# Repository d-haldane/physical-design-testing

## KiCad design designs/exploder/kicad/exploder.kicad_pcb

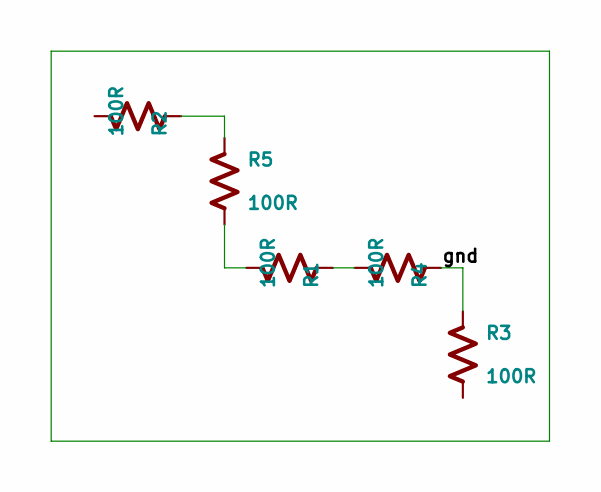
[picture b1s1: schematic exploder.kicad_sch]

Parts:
R1, R2, R3, R4, R5: 100R; Pkg0402; MPN RQ73C1E100RBTD

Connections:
gnd: R3.2, R4.1
r0_p1: R2.1, R5.2
r1_p1: R1.2, R5.1
r2_p1: R1.1, R4.2

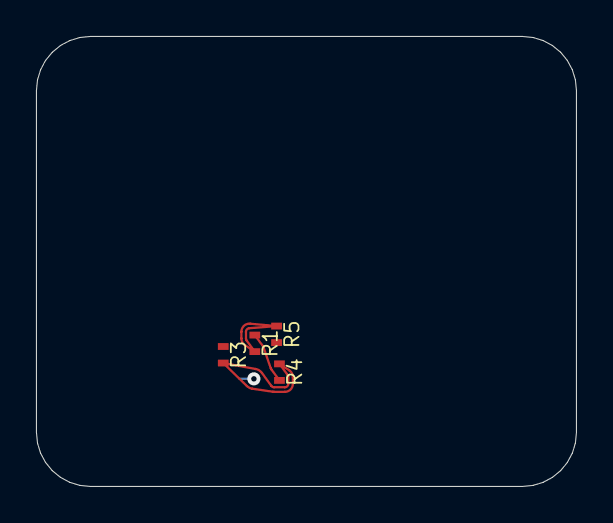
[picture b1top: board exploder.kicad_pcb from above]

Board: 4 copper layers, 30.0 x 25.0 mm, 5 parts (1 on the bottom side), 4 nets.

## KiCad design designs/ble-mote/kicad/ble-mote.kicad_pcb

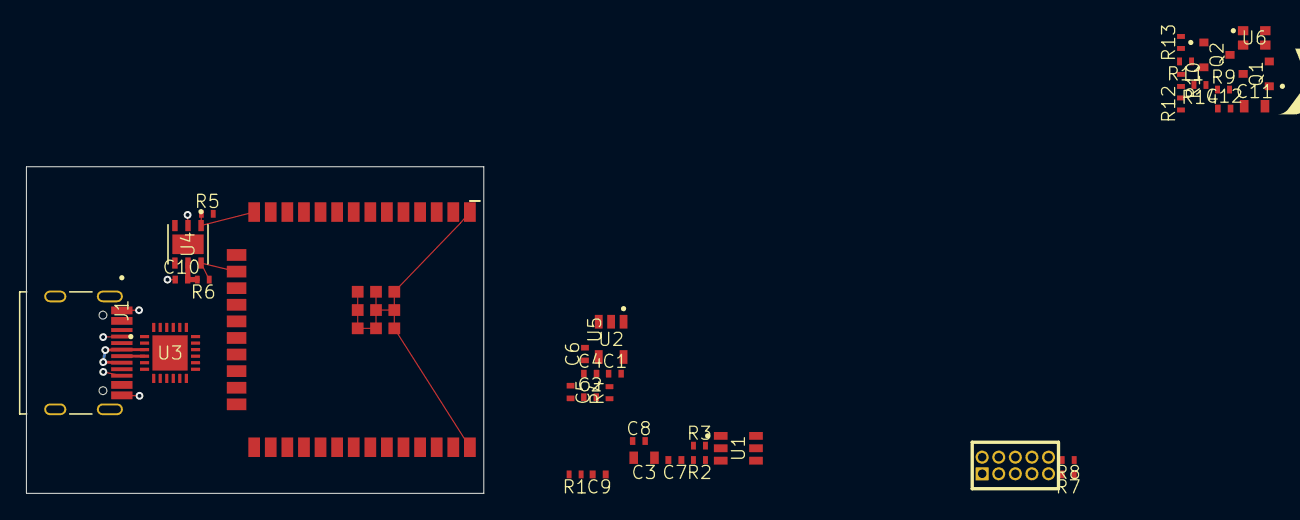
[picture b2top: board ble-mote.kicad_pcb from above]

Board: 4 copper layers, 35.0 x 25.0 mm, 37 parts (0 on the bottom side), 32 nets.

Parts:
C1, C2, C8, C10: 100n; Pkg0402_2
C3, C11: 10u; Pkg0603
C4, C5, C6, C12: 1u; Pkg0402_3
C7, C9: 4.7u; Pkg0402_1
H1: HDR_TH_10P_P1_27_V_F_R2_C5_S1_27_1
J1: LP_TYPE_C_31_M_12
JITX1: JITX_SM_LP
Q1, Q2: SOT95P280X100_3N
R1, R2: 5K1; Pkg0402_4
R3: 100K; Pkg0402_4
R4: 4K7; Pkg0402_4
R5, R6: 8K2; Pkg0402
R7, R8, R9, R10, R11: 10K; Pkg0402_4
R12, R13: 150R; Pkg0402_4
R14: 43R; Pkg0402_4
U1: SOT95P280X145_6N
U2: SOT95P280X145_5N
U3: QFN24
U4: SON100P300X300X80_7N
U5: ESP32_WROOM
U6: RGB_2020

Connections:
D+: J1.A6, J1.B6, U1.5, U3.3
D-: J1.A7, J1.B7, U1.6, U3.4
DTR_ECI: Q2.2, R10.1, U3.15
EN: C12.2, Q1.3, R9.2, U5.3
ESP-RX: U3.13, U5.34
ESP-TX: U3.12, U5.35
H-I2C_scl: R6.1, U4.6, U5.16
H-I2C_sda: R5.1, U4.1, U5.14
P3V3: C5.2, C10.2, C11.1, R4.2, R5.2, R6.2, R7.1, R8.1, R9.1, U2.5, U3.5, U4.5, U5.2, U6.4
P5V0: C3.1, C4.2, C6.1, H1.1, H1.2, U1.4, U2.1, U2.3, U3.7, U3.8
RTS_ECI: Q1.2, R11.1, U3.11
VBUS: C2.1, J1.A4-B9, J1.B4-A9, U1.1, U1.3
VDD: C8.2, C9.2, U3.6
VPP: C7.1, U3.16
b: Q1.1, R10.2
c: Q2.3, U5.25
cap_p1: C1.1, J1.13, J1.14, J1.15, J1.16, R3.1
control-pins0_timer: R12.1, U5.33
control-pins1_timer: R13.1, U5.12
control-pins2_timer: R14.1, U5.11
g: R13.2, U6.3
gnd: C1.2, C2.2, C3.2, C4.1, C5.1, C6.2, C7.2, C8.1, C9.1, C10.1, C11.2, C12.1, H1.3, H1.4, J1.A1-B12, J1.B1-A12, R1.2, R2.2, R3.2, U1.2, U2.2, U3.2, U3.25, U4.2, U5.1, U5.15, U5.38, U5.39, U5.40, U5.41, U5.42, U5.43, U5.44, U5.45, U5.46, U5.47
l_b: R14.2, U6.2
nRST: R4.1, U3.9
pc-ctrl0_gpio: H1.9, R7.2, U5.31
pc-ctrl1_gpio: H1.6, R8.2, U5.36
pc-uart_rx: H1.8, U5.10
pc-uart_tx: H1.10, U5.37
proc_q1_b: Q2.1, R11.2
r: R12.2, U6.1
rid_p1: J1.B5, R2.1
rid_rid_p1: J1.A5, R1.1

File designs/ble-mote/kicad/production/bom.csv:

Designator,Footprint,Quantity,Value,LCSC Part #
"C1, C10, C2",Pkg0402_3,3,100n,
"C11, C3",Pkg0603,2,10u,
"C12, C4, C5, C6",Pkg0402,4,1u,
"C7, C8",Pkg0402_3,2,4.7u,
H1,HDR_TH_10P_P1_27_V_F_R2_C5_S1_27_1,1,~,
J1,LP_TYPE_C_31_M_12,1,~,
JITX1,JITX_SM_LP,1,~,
"Q1, Q2",SOT95P280X100_3N,2,~,
"R1, R2",Pkg0402_2,2,5K1,
"R10, R11, R7, R8, R9",Pkg0402_2,5,10K,
"R12, R13",Pkg0402_1,2,150R,
R14,Pkg0402_2,1,43R,
R3,Pkg0402_2,1,100K,
R4,Pkg0402_2,1,4K7,
"R5, R6",Pkg0402_2,2,8K2,
"TP1, TP10, TP11, TP12, TP13, TP2, TP3, TP4, TP5, TP6, TP7, TP8, TP9",SMD_TESTPT,13,~,
U1,SOT95P280X145_6N,1,~,
U2,SOT95P280X145_5N,1,~,
U3,QFN24,1,~,
U4,SON100P300X300X80_7N,1,~,
U5,ESP32_WROOM,1,~,
U6,RGB_2020,1,~,

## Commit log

2023-03-22 100% completion
2023-03-24 Sourcing parts
2023-03-24 Bump ocdb
2023-03-28 realization issue
2023-03-28 Schematic export issue in kicad
2023-03-28 Missing Table Key in stabilization
2023-03-28 Exploded schematic nets
2023-03-28 A happy schematic layout I'm about to blow up
2023-03-29 Funky pin assignment on LED
2023-03-29 realization force
2023-03-30 Broke physical design by changing rules I think?
2023-03-30 update rules
2023-03-30 pin assignment partial-net
2023-03-30 Outline change
2023-03-30 Cutting corners
2023-03-30 Infinite loop
2023-03-30 realization error
2023-03-31 Physical design beautiful pre-update
2023-03-31 Stable schematic error
2023-03-31 Completed design
2023-03-31 Synchronization pin assignment
2023-03-31 RIP babby
2023-03-31 Clean house
2023-04-05 Update design files to new standard
2023-04-11 StableDesign unstable
2023-04-13 Add realization issue
2023-04-13 This file was always here
2023-04-18 Design contains routes lost on reload
2023-04-19 Fully routed
2023-04-19 Ordered version
2023-04-19 Add fab files
2023-05-16 realization cross on scratch.stanza
2023-05-16 3 route realization
